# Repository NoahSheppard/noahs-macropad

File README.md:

The firmware.

The reason for it being in a different branch is because of QMK really just wanting so badly to be on WSL's "internal" drive

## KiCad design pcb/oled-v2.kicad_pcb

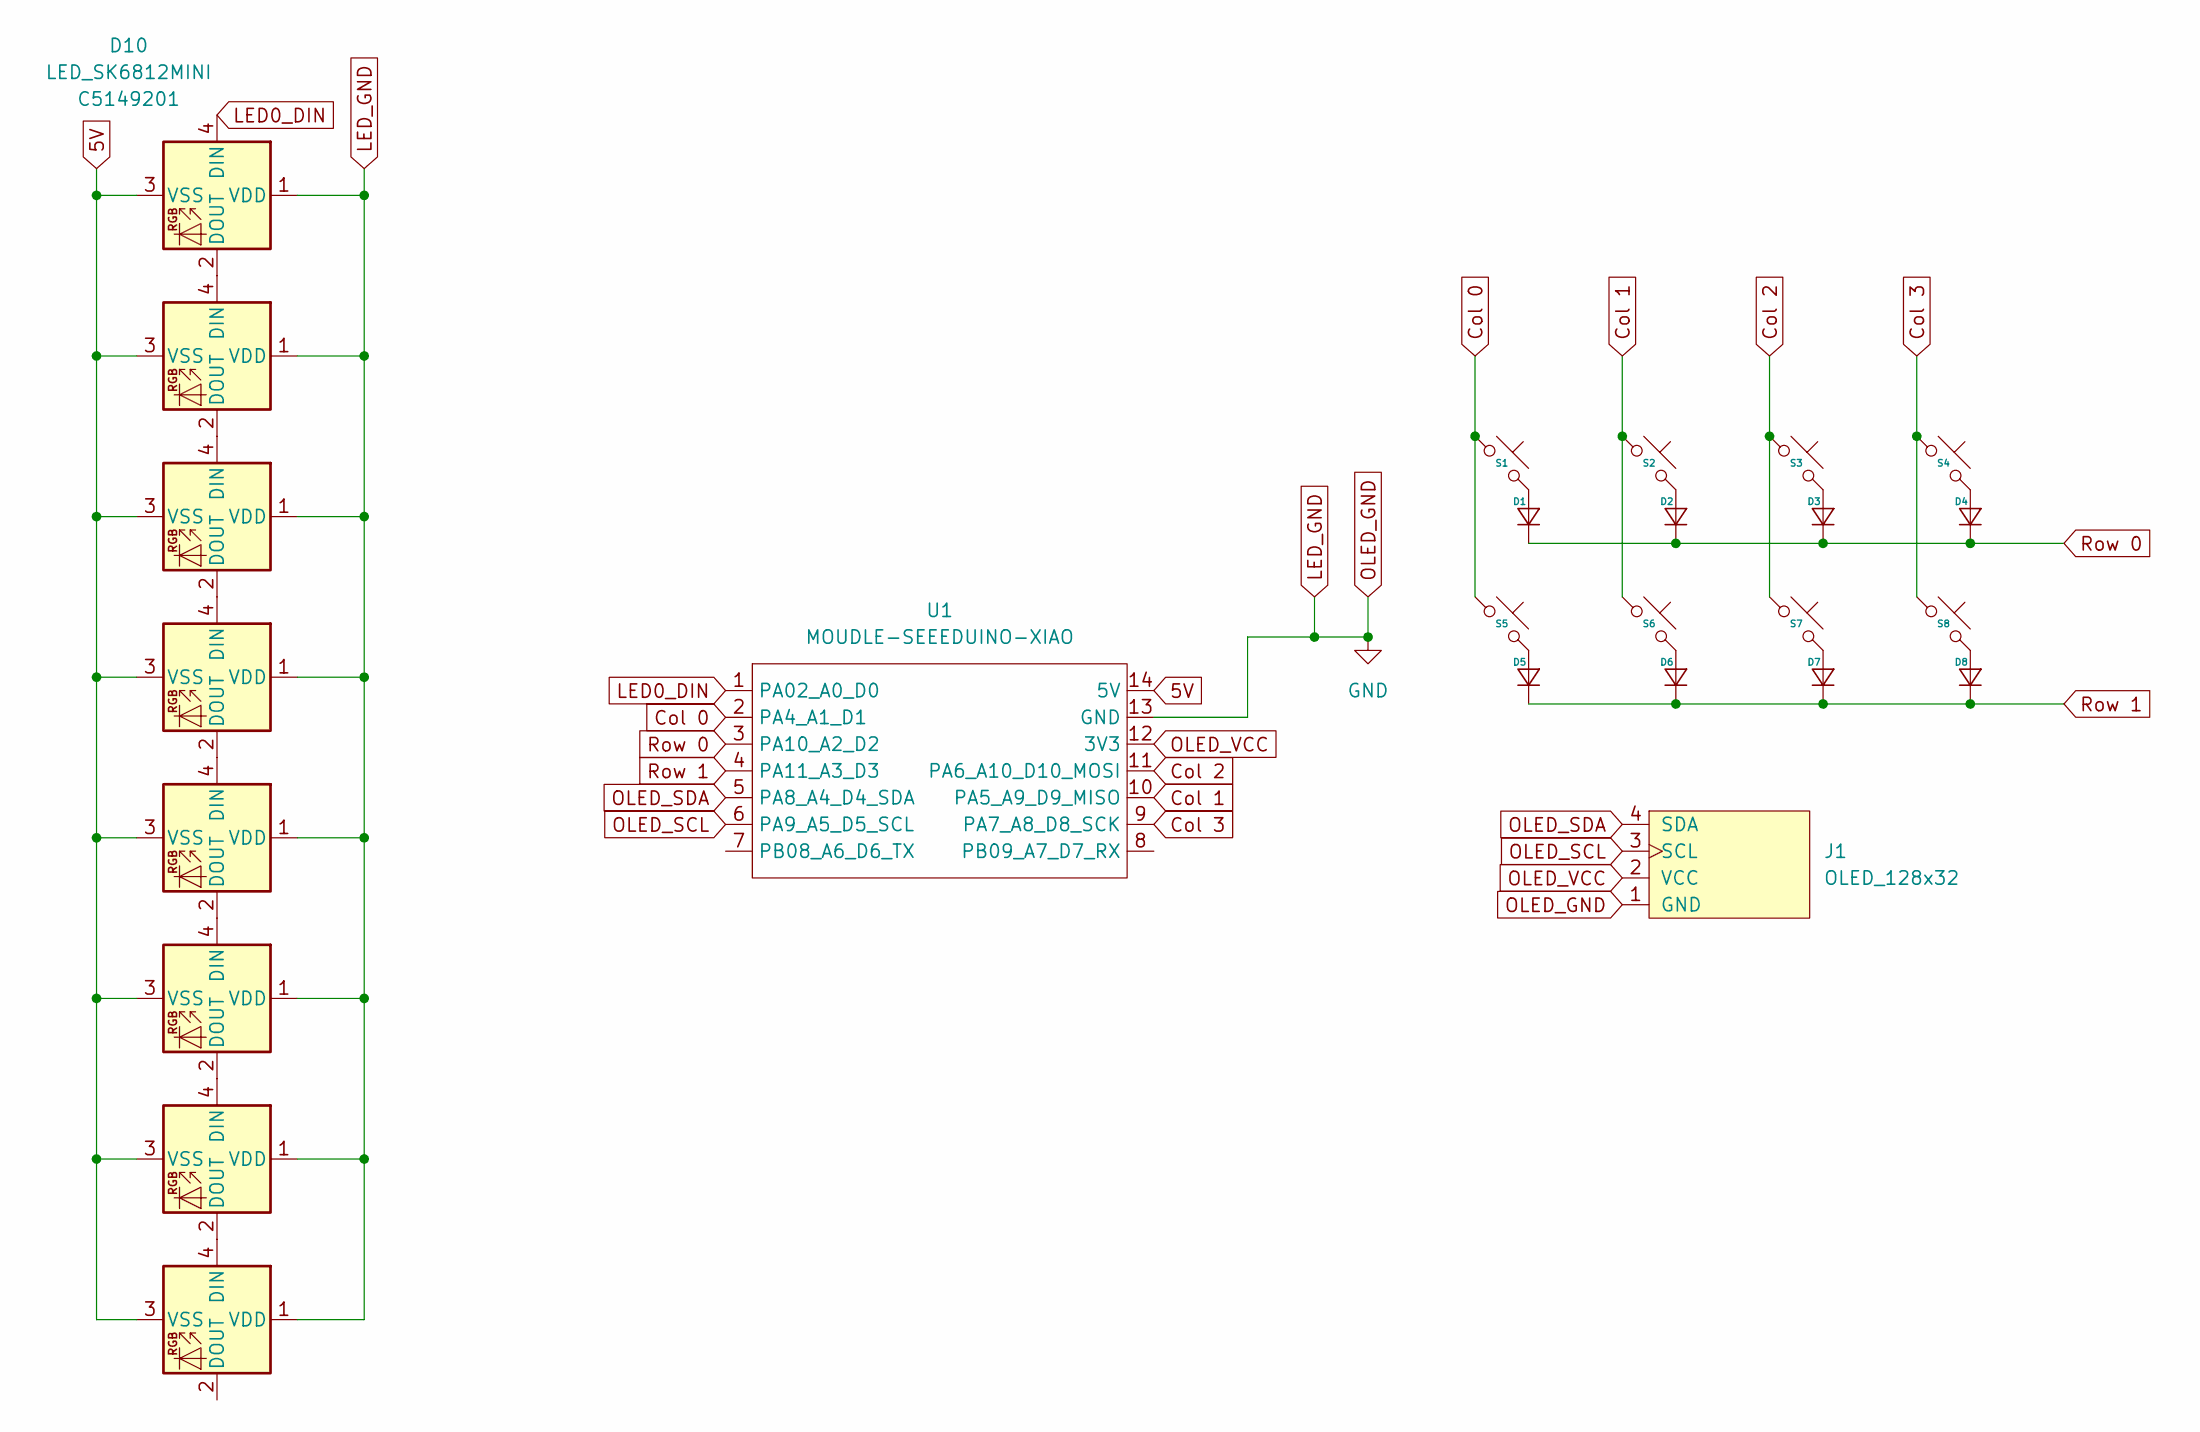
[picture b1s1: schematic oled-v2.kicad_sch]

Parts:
D1, D2, D3, D4, D5, D6, D7, D8: Diode_DO-35
D9, D10, D11, D12, D13, D14, D15, D16: LED_SK6812MINI; LCSC C5149201
J1: OLED_128x32
S1, S2, S3, S4, S5, S6, S7, S8: SW_Cherry_MX_1.00u_PCB
U1: MOUDLE-SEEEDUINO-XIAO; XIAO-Generic-Hybrid-14P-2.54-21X17.8MM

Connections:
5V: D9.3 (VSS), D10.3 (VSS), D11.3 (VSS), D12.3 (VSS), D13.3 (VSS), D14.3 (VSS), D15.3 (VSS), D16.3 (VSS), U1.14 (5V)
Col 0: S1.1, S5.1, U1.2 (PA4_A1_D1)
Col 1: S2.1, S6.1, U1.10 (PA5_A9_D9_MISO)
Col 2: S3.1, S7.1, U1.11 (PA6_A10_D10_MOSI)
Col 3: S4.1, S8.1, U1.9 (PA7_A8_D8_SCK)
LED0_DIN: D10.4 (DIN), U1.1 (PA02_A0_D0)
LED_GND: D9.1 (VDD), D10.1 (VDD), D11.1 (VDD), D12.1 (VDD), D13.1 (VDD), D14.1 (VDD), D15.1 (VDD), D16.1 (VDD), J1.1 (GND), U1.13 (GND)
unnamed: D1.2 (A), S1.2
unnamed: D2.2 (A), S2.2
unnamed: D3.2 (A), S3.2
unnamed: D4.2 (A), S4.2
unnamed: D5.2 (A), S5.2
unnamed: D6.2 (A), S6.2
unnamed: D7.2 (A), S7.2
unnamed: D8.2 (A), S8.2
unnamed: D9.4 (DIN), D10.2 (DOUT)
unnamed: D9.2 (DOUT), D11.4 (DIN)
unnamed: D11.2 (DOUT), D12.4 (DIN)
unnamed: D12.2 (DOUT), D13.4 (DIN)
unnamed: D13.2 (DOUT), D14.4 (DIN)
unnamed: D14.2 (DOUT), D15.4 (DIN)
unnamed: D15.2 (DOUT), D16.4 (DIN)
OLED_SCL: J1.3 (SCL), U1.6 (PA9_A5_D5_SCL)
OLED_SDA: J1.4 (SDA), U1.5 (PA8_A4_D4_SDA)
OLED_VCC: J1.2 (VCC), U1.12 (3V3)
Row 0: D1.1 (K), D2.1 (K), D3.1 (K), D4.1 (K), U1.3 (PA10_A2_D2)
Row 1: D5.1 (K), D6.1 (K), D7.1 (K), D8.1 (K), U1.4 (PA11_A3_D3)

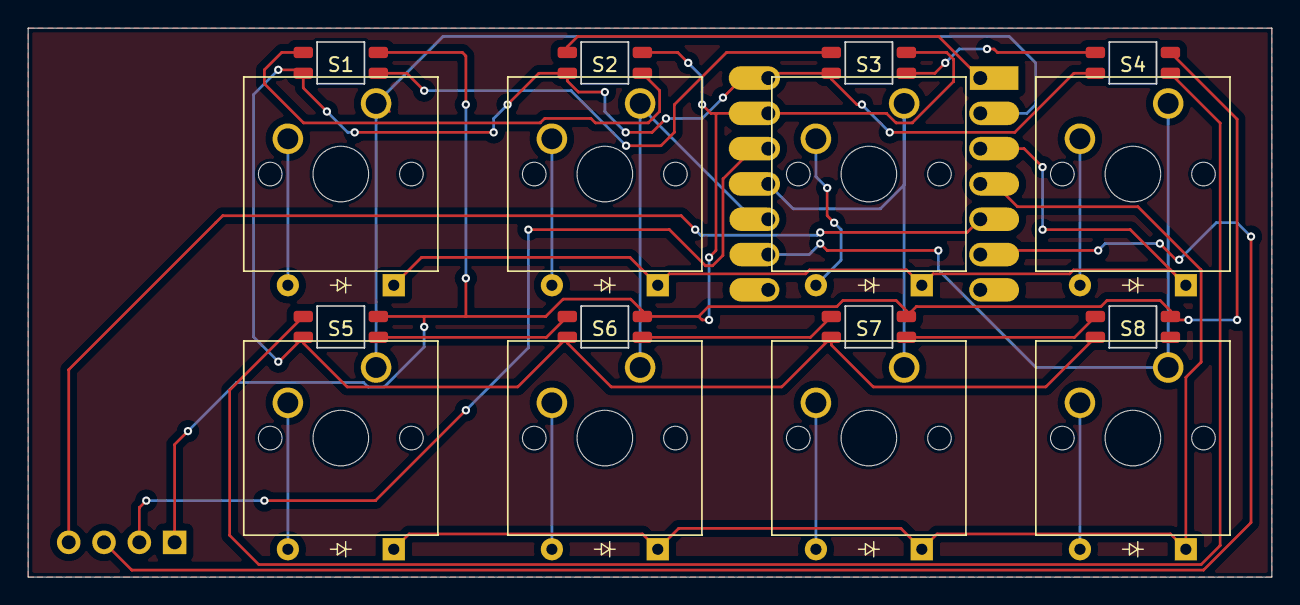
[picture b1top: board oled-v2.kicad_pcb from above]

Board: 2 copper layers, 89.4 x 39.4 mm, 26 parts (1 on the bottom side), 27 nets.

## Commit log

2026-02-19 redesign with oled screen
2026-02-20 finished the case! finally figured out how to make screwholes and the likes, got all the custom holes designed, and look at the bottom....
2026-02-20 finalised cad, reworked the letters in the back so its all the one body and wouldn't just fafll out... - generated gerbers. Firmware is next
2026-02-20 few readme changes
2026-02-20 firmware woohoo (very basic just to get a working prototype in hand before i start fucking with proper firmware...
2026-02-20 initial basic firmware
2026-02-20 basic readme it is 12 am i am tired
2026-02-20 Firmware update, initial layering but no ability to change, that will happen later (gui maybe? this could be huge chat)
2026-02-20 oled implementation
2026-02-21 tertis hehe
2026-02-21 added doom shareware, going to butcher to get to work on 128x32x1 rather than 320x200x8 minimum lol
2026-02-22 somehow forgot to export the actual thing as a f3d file because im super cool I guess? + cheeky off camera firmware grind (its gonna be super cool I proimse)
